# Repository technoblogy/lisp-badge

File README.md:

# Lisp Badge
A handheld computer with a self-contained keyboard and display that you can program in Lisp.

Version 6 updates the uLisp firmware to uLisp 4.3, adding support for arrays, and built-in documentation (see http://www.ulisp.com/show?41E0).

It also adds some extra key combinations to allow you to enter additional characters from the keyboard:

| Character | Combination |
| --------- | ----------- |
| ~  | Shift+ESC |
| % | Shift+DEL |
| : | Shift+ENTER |
| ? | Shift+SPACE |

For information about building the Lisp Badge see: http://www.technoblogy.com/show?2AEE

For information about programming the Lisp badge see: http://www.ulisp.com/show?2L0C

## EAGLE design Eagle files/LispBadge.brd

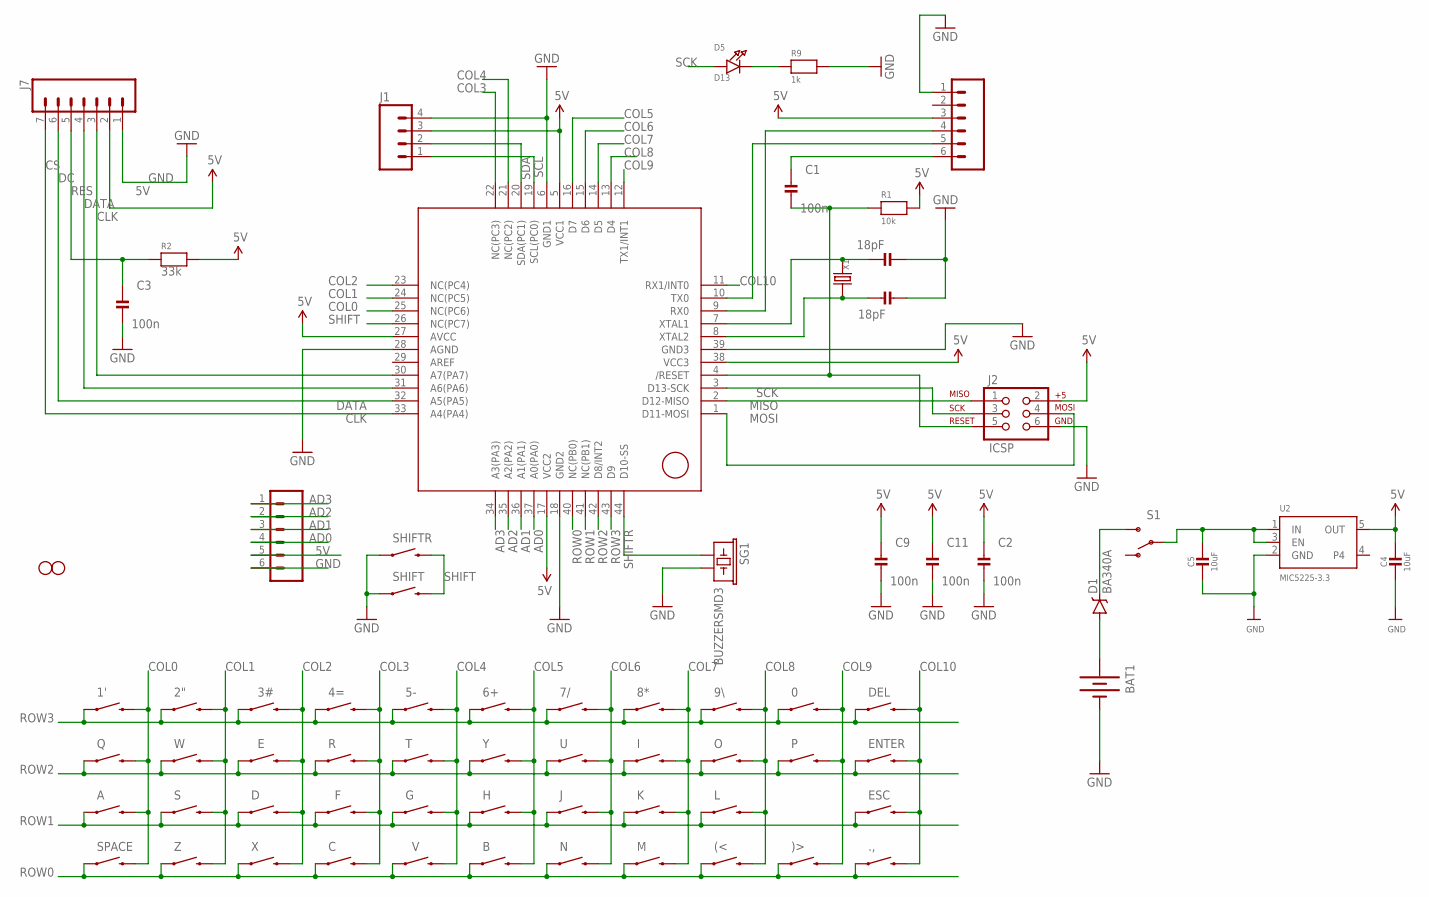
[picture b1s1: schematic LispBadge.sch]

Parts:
0, 1', 2", 3#, 4=, 5-, 6+, 7/, 8*, 9\\, .,: SWITCH-MOMENTARY-2PTH; TACTILE-PTH
(<: SWITCH-MOMENTARY-2PTH; TACTILE-PTH
)>: SWITCH-MOMENTARY-2PTH; TACTILE-PTH
A: SWITCH-MOMENTARY-2PTH; TACTILE-PTH
B: SWITCH-MOMENTARY-2PTH; TACTILE-PTH
BAT1: BATTERYAAA-KIT; BATTERY-AAA-KIT
C: SWITCH-MOMENTARY-2PTH; TACTILE-PTH
C1, C2, C3, C9, C11: 100n; _0805MP
C4, C5: 10uF; 0805-NO
C12, C13: 18pF; _0805MP
D: SWITCH-MOMENTARY-2PTH; TACTILE-PTH
D1: BA340A; SMA-DIODE
D5: D13; CHIPLED_0805_NOOUTLINE
DEL: SWITCH-MOMENTARY-2PTH; TACTILE-PTH
E: SWITCH-MOMENTARY-2PTH; TACTILE-PTH
ENTER: SWITCH-MOMENTARY-2PTH; TACTILE-PTH
ESC: SWITCH-MOMENTARY-2PTH; TACTILE-PTH
F: SWITCH-MOMENTARY-2PTH; TACTILE-PTH
G: SWITCH-MOMENTARY-2PTH; TACTILE-PTH
H: SWITCH-MOMENTARY-2PTH; TACTILE-PTH
I: SWITCH-MOMENTARY-2PTH; TACTILE-PTH
J: SWITCH-MOMENTARY-2PTH; TACTILE-PTH
J1: M04LONGPADS; 1X04_LONGPADS
J2: ICSP; 2X3
J7: M07; 1X07
JP1, JP11: M06LONGPADS; 1X06_LONGPADS
JP4, JP5: STAND-OFF
K: SWITCH-MOMENTARY-2PTH; TACTILE-PTH
L: SWITCH-MOMENTARY-2PTH; TACTILE-PTH
M: SWITCH-MOMENTARY-2PTH; TACTILE-PTH
N: SWITCH-MOMENTARY-2PTH; TACTILE-PTH
O: SWITCH-MOMENTARY-2PTH; TACTILE-PTH
P: SWITCH-MOMENTARY-2PTH; TACTILE-PTH
Q: SWITCH-MOMENTARY-2PTH; TACTILE-PTH
R: SWITCH-MOMENTARY-2PTH; TACTILE-PTH
R1: 10k; _0805MP
R2: 33k; _0805MP
R9: 1k; _0805MP
S: SWITCH-MOMENTARY-2PTH; TACTILE-PTH
S1: SWITCH-SPDTPTH; SWITCH-SPDT
SG1: BUZZERSMD3; BUZZER-CMT1102
SHIFT: SWITCH-MOMENTARY-2PTH; TACTILE-PTH
SHIFTR: SWITCH-MOMENTARY-2PTH; TACTILE-PTH
SPACE: SWITCH-MOMENTARY-2PTH; TACTILE-PTH
T: SWITCH-MOMENTARY-2PTH; TACTILE-PTH
U: SWITCH-MOMENTARY-2PTH; TACTILE-PTH
U2: MIC5225-3.3; SOT23-5
U3: ATMEGA1284P; TQFP44
V: SWITCH-MOMENTARY-2PTH; TACTILE-PTH
W: SWITCH-MOMENTARY-2PTH; TACTILE-PTH
X: SWITCH-MOMENTARY-2PTH; TACTILE-PTH
X1: CRYSTAL-0500290P1; 2P-SMD-5.0X3.2
Y: SWITCH-MOMENTARY-2PTH; TACTILE-PTH
Z: SWITCH-MOMENTARY-2PTH; TACTILE-PTH

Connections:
5V: C2.1, C4.1, C9.1, C11.1, J1.3, J2.2, J7.2, JP1.3, JP11.5, R1.2, R2.2, U2.5 (OUT), U3.5 (VCC1), U3.17 (VCC2), U3.27 (AVCC), U3.38 (VCC3)
AD0: JP11.4, U3.37 (A0(PA0))
AD1: JP11.3, U3.36 (A1(PA1))
AD2: JP11.2, U3.35 (A2(PA2))
AD3: JP11.1, U3.34 (A3(PA3))
CLK: J7.3, U3.30 (A7(PA7))
COL0: 1'.3 (2), A.3 (2), Q.3 (2), SPACE.3 (2), U3.25 (NC(PC6))
COL1: 2".3 (2), S.3 (2), U3.24 (NC(PC5)), W.3 (2), Z.3 (2)
COL2: 3#.3 (2), D.3 (2), E.3 (2), U3.23 (NC(PC4)), X.3 (2)
COL3: 4=.3 (2), C.3 (2), F.3 (2), R.3 (2), U3.22 (NC(PC3))
COL4: 5-.3 (2), G.3 (2), T.3 (2), U3.21 (NC(PC2)), V.3 (2)
COL5: 6+.3 (2), B.3 (2), H.3 (2), U3.16 (D7), Y.3 (2)
COL6: 7/.3 (2), J.3 (2), N.3 (2), U.3 (2), U3.15 (D6)
COL7: 8*.3 (2), I.3 (2), K.3 (2), M.3 (2), U3.14 (D5)
COL8: 9\\.3 (2), (<.3 (2), L.3 (2), O.3 (2), U3.13 (D4)
COL9: 0.3 (2), )>.3 (2), P.3 (2), U3.12 (TX1/INT1)
COL10: .,.3 (2), DEL.3 (2), ENTER.3 (2), ESC.3 (2), U3.11 (RX1/INT0)
CS: J7.7, U3.33 (A4(PA4))
DATA: J7.4, U3.31 (A6(PA6))
DC: J7.6, U3.32 (A5(PA5))
GND: BAT1.GND@1 (-), C2.2, C3.2, C4.2, C5.2, C9.2, C11.2, C12.1, C13.1, J1.4, J2.6, J7.1, JP1.1, JP11.6, R9.2, SG1.2, SHIFT.1, SHIFTR.1, U2.2 (GND), U3.6 (GND1), U3.18 (GND2), U3.28 (AGND), U3.39 (GND3)
MISO: J2.1, U3.2 (D12-MISO)
MOSI: J2.4, U3.1 (D11-MOSI)
unnamed: BAT1.PWR@1 (+), D1.A
unnamed: D1.C, S1.3 (S)
unnamed: D5.C, R9.1
unnamed: C5.1, S1.2, U2.1 (IN), U2.3 (EN)
unnamed: C13.2, U3.8 (XTAL2), X1.2
unnamed: C12.2, U3.7 (XTAL1), X1.1
unnamed: C1.2, J2.5, R1.1, U3.4 (/RESET)
unnamed: C1.1, JP1.6
RES: C3.1, J7.5, R2.1
ROW0: (<.1, )>.1, .,.1, B.1, C.1, M.1, N.1, SPACE.1, U3.40 (NC(PB0)), V.1, X.1, Z.1
ROW1: A.1, D.1, ESC.1, F.1, G.1, H.1, J.1, K.1, L.1, S.1, U3.41 (NC(PB1))
ROW2: E.1, ENTER.1, I.1, O.1, P.1, Q.1, R.1, T.1, U.1, U3.42 (D8/INT2), W.1, Y.1
ROW3: 0.1, 1'.1, 2".1, 3#.1, 4=.1, 5-.1, 6+.1, 7/.1, 8*.1, 9\\.1, DEL.1, U3.43 (D9)
RX-I: JP1.4, U3.9 (RX0)
SCK: D5.A, J2.3, U3.3 (D13-SCK)
SCL: J1.1, U3.19 (SCL(PC0))
SDA: J1.2, U3.20 (SDA(PC1))
SHIFT: SHIFT.3 (2), SHIFTR.3 (2), U3.26 (NC(PC7))
SHIFTR: SG1.1, U3.44 (D10-SS)
TX-O: JP1.5, U3.10 (TX0)

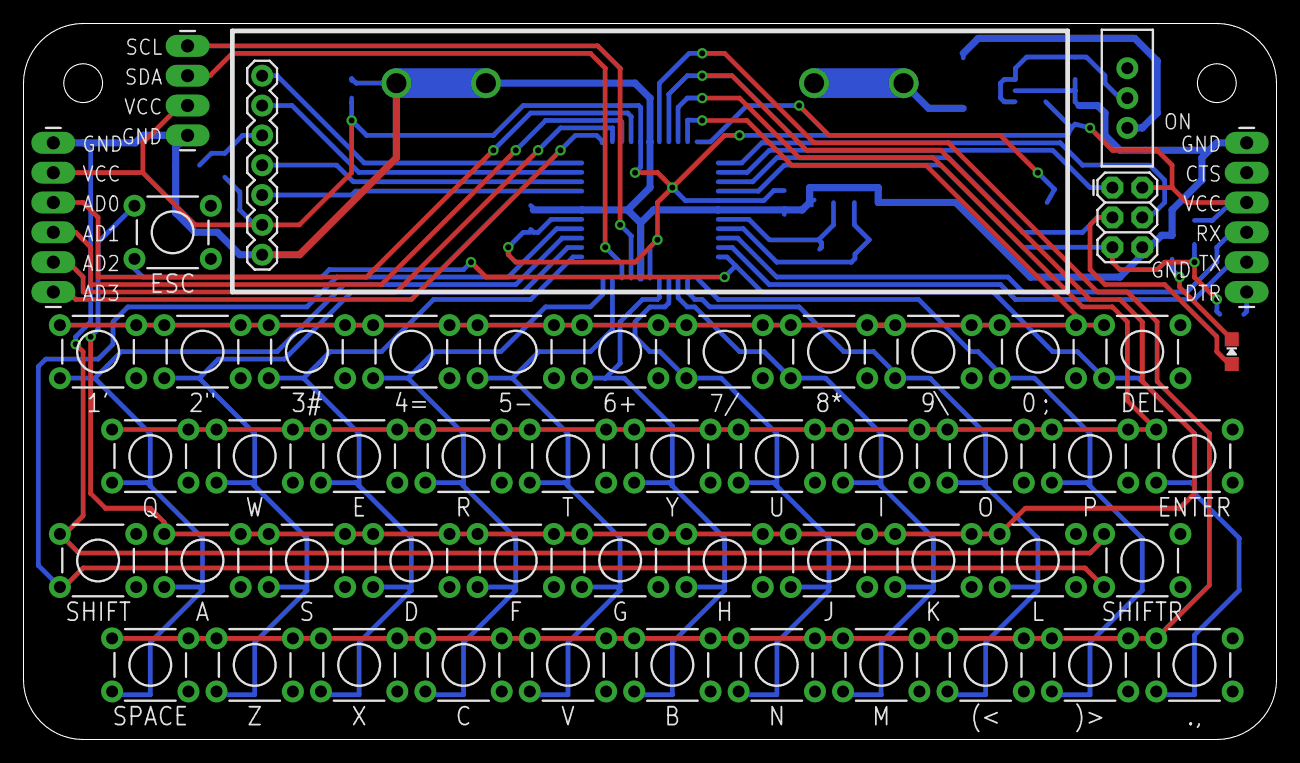
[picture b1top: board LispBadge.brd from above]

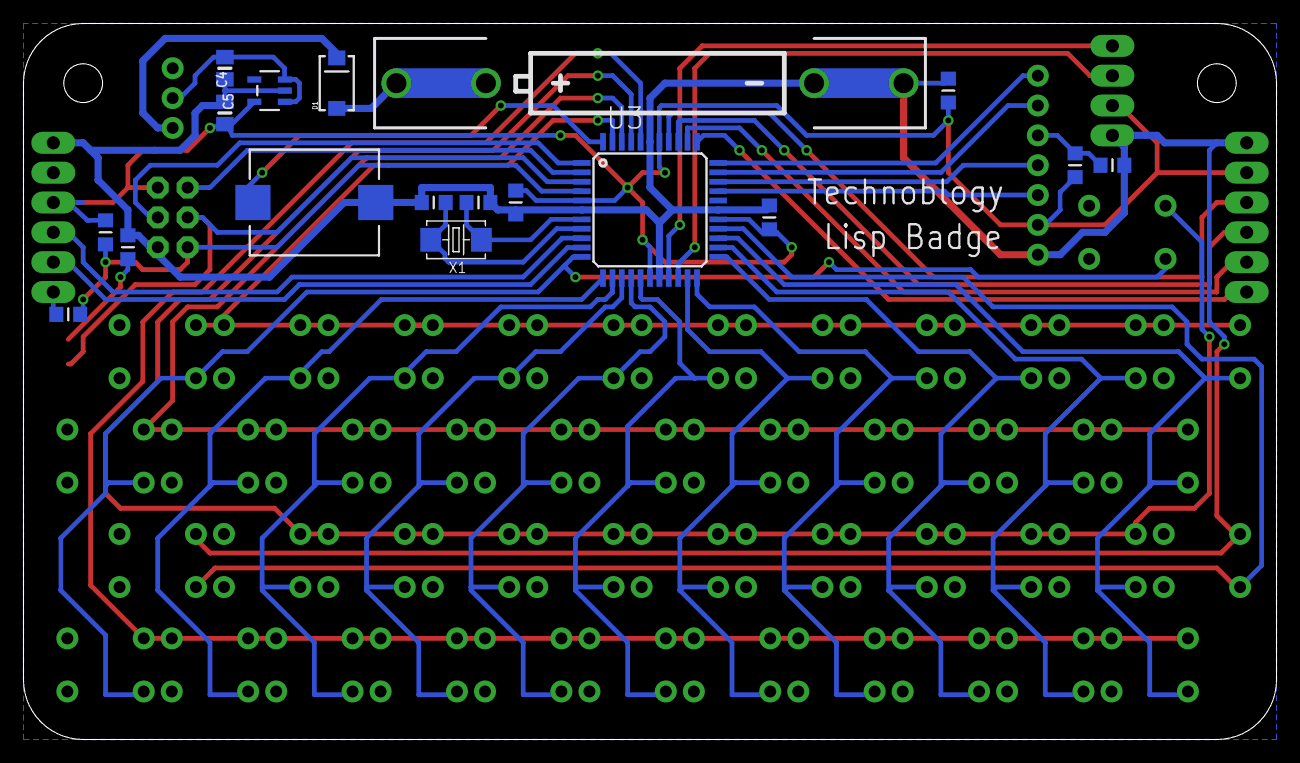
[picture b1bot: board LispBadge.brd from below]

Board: 2 copper layers, 106.7 x 61.0 mm, 72 parts (18 on the bottom side), 43 nets.

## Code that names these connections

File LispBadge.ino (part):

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"Prints its argument to a string, and returns the string.\n"
"Characters and strings are printed with quotation marks and escape characters,\n"
"in a format that will be suitable for read-from-string.";
const char doc135[] PROGMEM = "(ash value shift)\n"
"Returns the result of bitwise shifting value by shift bits. If shift is positive, value is shifted to the left.";
const char doc136[] PROGMEM = "(logbitp bit value)\n"
"Returns t if bit number bit in value is a '1', and nil if it is a '0'.";
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// Lisp Badge terminal and keyboard support

// These are the bit positions in PORTA
int const clk = 7;   // PA7
int const data = 6;  // PA6
int const dc = 5;    // PA5
int const cs = 4;    // PA4

// Terminal **********************************************************************************

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  static uint8_t column = 0, nokey = 0;
  uint8_t rows, shift, row;
  // Check rows and shift key
  shift = (PINC & 1<<PINC7) ? 0 : 1;
  rows = PINB & RowBits;
  if (rows == RowBits) { if (nokey < 11) nokey++; }
  else if (nokey < 11) nokey = 0;
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
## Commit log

2019-01-10 Version 1 - 10th January 2019
2019-01-11 Version 1a - 11th January 2019
    Fixed typo in plot.
2019-01-12 Version 1b - 12th January 2019
    Fix compile error.
2019-02-07 Version 1c - 7th February 2019
    Fixes a keyboard problem on some boards, and adds beep to the piezo speaker.
2019-05-26 Version 2 - 26th May 2019
    Updated uLisp to Version 2.7
2020-07-10 Version 3 - 10th July 2020
    Updates uLisp to AVR Version 3.3a
2021-04-04 Version 4 - 4th April 2021
    Updates uLisp to Version 3.6
2022-01-23 Version 5 - 23rd January 2022
    Updates uLisp to version 4.1a.
2022-09-23 Version 6 - 22nd September 2022
    Updated to uLisp 4.3, with arrays and built-in documentation.

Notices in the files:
LispBadge.ino:
Licensed under the MIT license: https://opensource.org/licenses/MIT
parts and their libraries:
SparkFun-Electromechanical: Licensing: Creative Commons ShareAlike 4.0 International - https://creativecommons.org/licenses/by-sa/4.0
SparkFun-Connectors: Licensing: CC v3.0 Share-Alike You are welcome to use this library for commercial purposes.
